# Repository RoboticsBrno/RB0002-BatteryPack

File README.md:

# RB0002-BatteryPack

Universal 2 cells Li-Ion battery pack with separate USB charger PCB for robot
power supplying.

This battery pack is designed for continuous 8.4 V / 15 A.

View this project on [CADLAB.io](https://cadlab.io/project/22740/).

License: [CC BY-SA 4.0](https://creativecommons.org/licenses/by-sa/4.0/?)

## Repository Structure

- `batteryPack` contains the main schematics and board drawing
- `doc` contains CubeMX pinout of the MCU, resistor calculation spreadsheet,
  etc.
- `footprints` contains the board-specific footprints
- `symbols` contains the board-specific symbols
- `tools` contains few scripts for automatization

## Building

Simply call `make` in the top-top level directory. The `build` directory will
them contain:

- split boards for the charger and the battery pack
- zipped gerbers for the boards you can directly use for manufacturing

Makefile uses [KiKit](https://github.com/yaqwsx/KiKit), therefore, it has to be
available on your system.

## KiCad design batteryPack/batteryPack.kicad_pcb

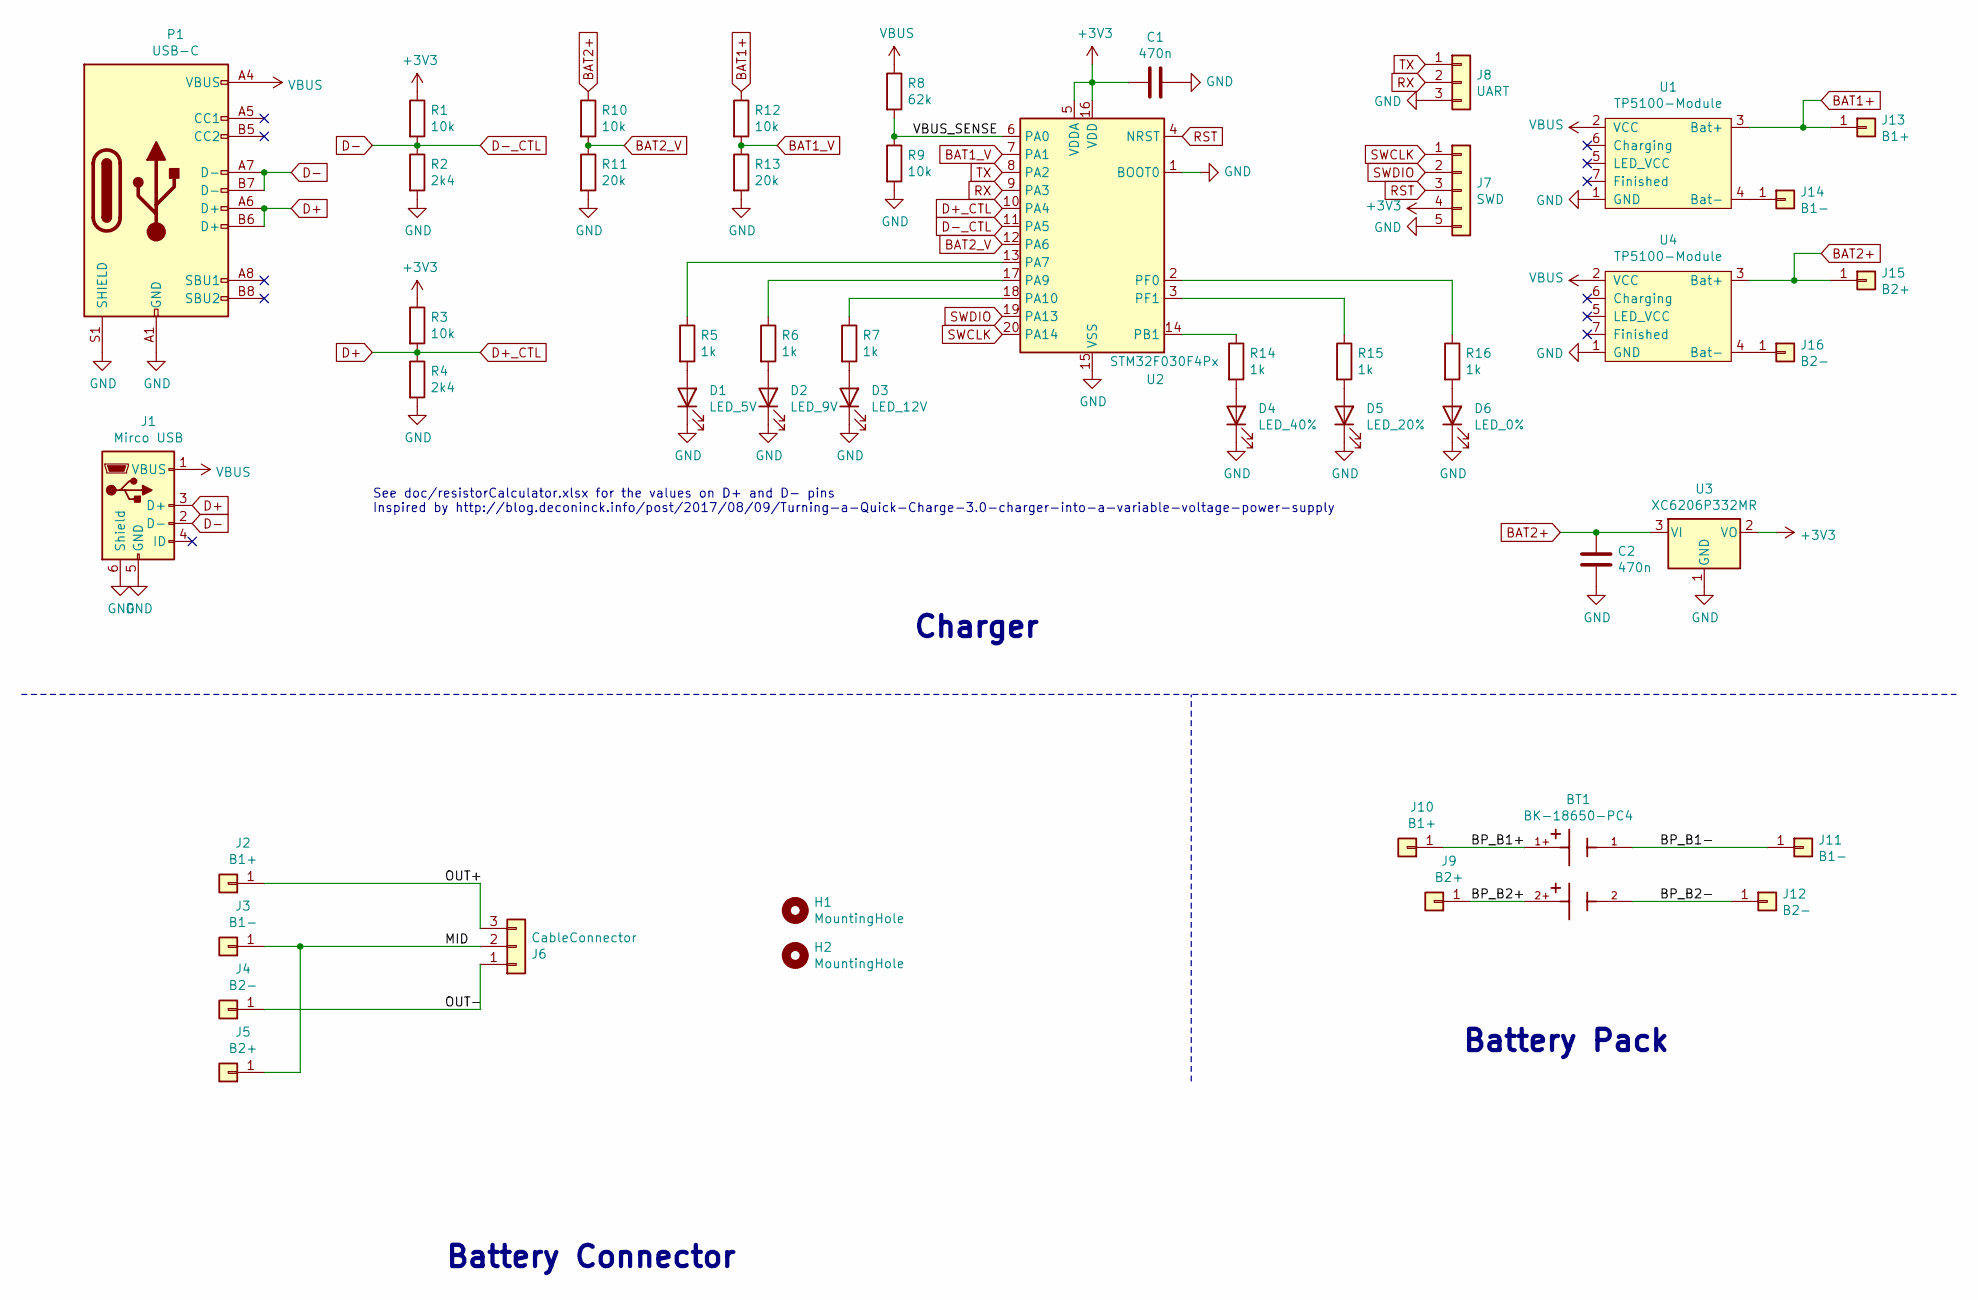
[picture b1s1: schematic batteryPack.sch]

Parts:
BT1: BK-18650-PC4; BAT_BK-18650-PC4
C1, C2: 470n; C_0603_1608Metric_Pad1.05x0.95mm_HandSolder
D1: LED_5V; LED_0603_1608Metric_Pad1.05x0.95mm_HandSolder
D2: LED_9V; LED_0603_1608Metric_Pad1.05x0.95mm_HandSolder
D3: LED_12V; LED_0603_1608Metric_Pad1.05x0.95mm_HandSolder
D4: LED_40%; LED_0603_1608Metric_Pad1.05x0.95mm_HandSolder
D5: LED_20%; LED_0603_1608Metric_Pad1.05x0.95mm_HandSolder
D6: LED_0%; LED_0603_1608Metric_Pad1.05x0.95mm_HandSolder
H1, H2: MountingHole; MountingHole_3.2mm_M3
J1: Mirco USB; USB_Micro-B_Wuerth_629105150521_CircularHoles
J2: B1+; 2mm_Banana-Vertical
J3: B1-; 2mm_Banana-Vertical
J4: B2-; 2mm_Banana-Vertical
J5: B2+; 2mm_Banana-Vertical
J6: CableConnector; Terminal_1x03_P5.08mm_Horizontal
J7: SWD; PinHeader_1x05_P2.54mm_Vertical
J8: UART; PinHeader_1x03_P2.54mm_Vertical
J9: B2+; 2mm_Banana-Socket
J10: B1+; 2mm_Banana-Socket
J11: B1-; 2mm_Banana-Socket
J12: B2-; 2mm_Banana-Socket
J13: B1+; 2mm_Banana-Plug
J14: B1-; 2mm_Banana-Plug
J15: B2+; 2mm_Banana-Plug
J16: B2-; 2mm_Banana-Plug
P1: USB-C; USB_C_Female-16Pin-HPJF
R1, R3, R9, R10, R12: 10k; R_0603_1608Metric_Pad1.05x0.95mm_HandSolder
R2, R4: 2k4; R_0603_1608Metric_Pad1.05x0.95mm_HandSolder
R5, R6, R7, R14, R15, R16: 1k; R_0603_1608Metric_Pad1.05x0.95mm_HandSolder
R8: 62k; R_0603_1608Metric_Pad1.05x0.95mm_HandSolder
R11, R13: 20k; R_0603_1608Metric_Pad1.05x0.95mm_HandSolder
U1, U4: TP5100-Module
U2: STM32F030F4Px; TSSOP-20_4.4x6.5mm_P0.65mm
U3: XC6206P332MR; SOT-23

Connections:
+3V3: C1.2, J7.4, R1.1, R3.1, U2.5 (VDDA), U2.16 (VDD), U3.2 (VO)
/BP_B1+: BT1.1+, J10.1
/BP_B1-: BT1.1 (1-), J11.1
/BP_B2+: BT1.2+, J9.1
/BP_B2-: BT1.2 (2-), J12.1
/MID: J3.1, J5.1, J6.2
/OUT+: J2.1, J6.3
/OUT-: J4.1, J6.1
/VBUS_SENSE: R8.2, R9.1, U2.6 (PA0)
BAT1+: J13.1, R12.1, U1.3 (Bat+)
BAT1_V: R12.2, R13.1, U2.7 (PA1)
BAT2+: C2.2, J15.1, R10.1, U3.3 (VI), U4.3 (Bat+)
BAT2_V: R10.2, R11.1, U2.12 (PA6)
D+: J1.3 (D+), P1.A6 (D+), P1.B6 (D+), R3.2, R4.1, U2.10 (PA4)
D-: J1.2 (D-), P1.A7 (D-), P1.B7 (D-), R1.2, R2.1, U2.11 (PA5)
GND: C1.1, C2.1, D1.1 (K), D2.1 (K), D3.1 (K), D4.1 (K), D5.1 (K), D6.1 (K), J1.5 (GND), J1.6 (Shield), J7.5, J8.3, P1.A1 (GND), P1.A12 (GND), P1.B1 (GND), P1.B12 (GND), P1.S1 (SHIELD), R2.2, R4.2, R9.2, R11.2, R13.2, U1.1 (GND), U2.1 (BOOT0), U2.15 (VSS), U3.1 (GND), U4.1 (GND)
unnamed: D1.2 (A), R5.2
unnamed: D2.2 (A), R6.2
unnamed: D3.2 (A), R7.2
unnamed: D4.2 (A), R14.2
unnamed: D5.2 (A), R15.2
unnamed: D6.2 (A), R16.2
unnamed: J14.1, U1.4 (Bat-)
unnamed: J16.1, U4.4 (Bat-)
unnamed: R5.1, U2.13 (PA7)
unnamed: R6.1, U2.17 (PA9)
unnamed: R7.1, U2.18 (PA10)
unnamed: R14.1, U2.14 (PB1)
unnamed: R15.1, U2.3 (PF1)
unnamed: R16.1, U2.2 (PF0)
RST: J7.3, U2.4 (NRST)
RX: J8.2, U2.9 (PA3)
SWCLK: J7.1, U2.20 (PA14)
SWDIO: J7.2, U2.19 (PA13)
TX: J8.1, U2.8 (PA2)
VBUS: J1.1 (VBUS), P1.A4 (VBUS), P1.A9 (VBUS), P1.B4 (VBUS), P1.B9 (VBUS), R8.1, U1.2 (VCC), U4.2 (VCC)

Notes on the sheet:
Battery Pack
Charger
Battery Connector
See doc/resistorCalculator.xlsx for the values on D+ and D- pins Inspired by http://blog.deconinck.info/post/2017/08/09/Turning-a-Quick-Charge-3.0-charger-into-a-variable-voltage-power-supply

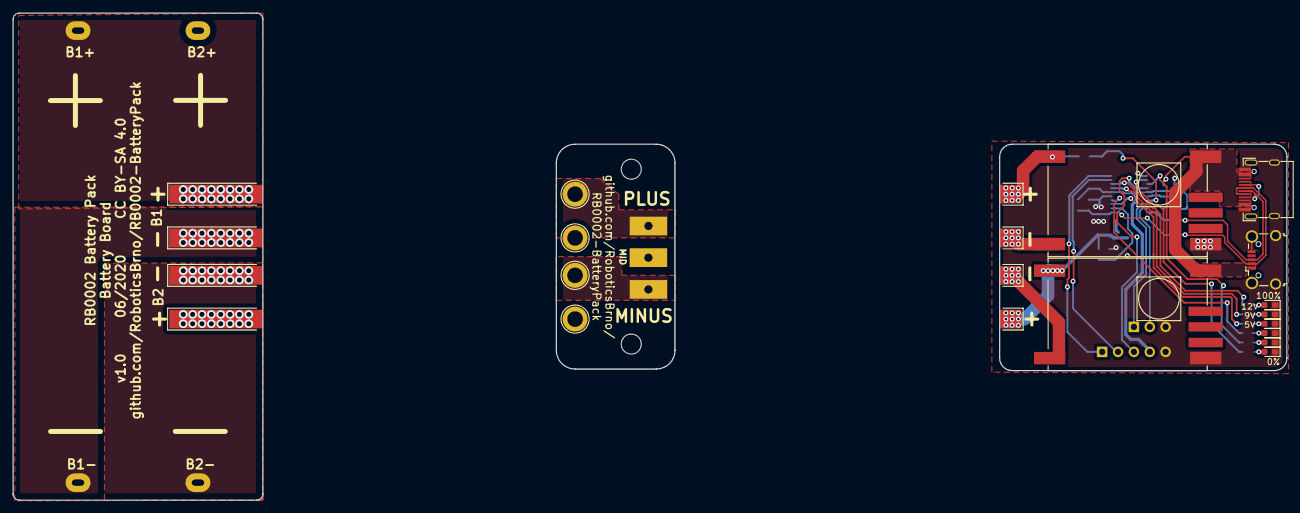
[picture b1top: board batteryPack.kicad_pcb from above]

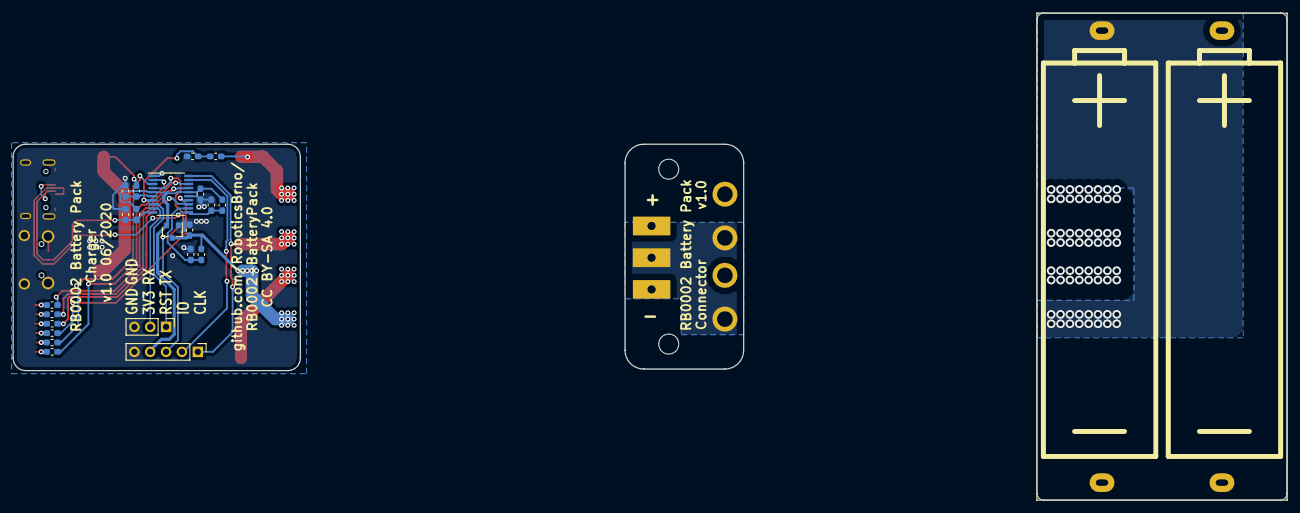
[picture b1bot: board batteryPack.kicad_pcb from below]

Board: 2 copper layers, 204.0 x 78.0 mm, 48 parts (23 on the bottom side), 36 nets.

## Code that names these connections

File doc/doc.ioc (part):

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Mcu.Name=STM32F030F4Px
Mcu.Package=TSSOP20
Mcu.UserName=STM32F030F4Px
PA0.Mode=IN0
PA0.Signal=ADC_IN0
PA1.Mode=IN1
PA1.Signal=ADC_IN1
PA10.Signal=GPIO_Output
PA13.Mode=Serial_Wire
PA13.Signal=SYS_SWDIO
PA14.Mode=Serial_Wire
PA14.Signal=SYS_SWCLK
PA2.Mode=Asynchronous
PA2.Signal=USART1_TX
PA3.Mode=Asynchronous
PA3.Signal=USART1_RX
PA6.Mode=IN6
PA6.Signal=ADC_IN6
PA7.Signal=GPIO_Output
PA9.Signal=GPIO_Output
PB1.Signal=GPIO_Output
PF0-OSC_IN.Signal=GPIO_Output
PF1-OSC_OUT.Signal=GPIO_Output
board=custom

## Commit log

2020-03-31 Prepare initial structure
2020-03-31 README.md: Add info about battery pack and USB charger
2020-04-01 Add documentation
2020-04-01 Finish first draft of the schematics
2020-04-01 Add fooprints
2020-04-01 Sketch out initial component layout
2020-04-01 Route battery and the connector
2020-04-01 Route the charger
2020-04-01 Make the labels nice
2020-04-01 Update Makefile for all three subboards
2020-04-02 Add battery holder 3D model
2020-04-02 Fine tune the board based on the feedback
2020-04-07 Migrate Makefile to KiKit
2020-04-08 Generate page using KiKit
2020-04-08 Add radius to panels
2020-04-21 Fine tune TP5100 footprint
2020-04-21 Migrate to KiKit 0.3
2020-04-26 Fix erroreous charger extraction
2020-04-29 Swap layers on battery board
2020-04-29 Add tenons and handle to the battery
2020-04-29 Change connector to screw terminal
2020-05-05 Tune pull handle and battery panel
2020-05-06 Add battery voltage signalization
2020-05-08 Add silkscreen text + LICENSE
    - add version info text to Charger board
    - add +/- text for Charger and Connector board
    - add license Creative Commons BY-SA 4.0
2020-06-17 Remove tenons from the battery
2020-06-17 Make ptich of battery holder smaller
2020-06-17 Mark the battery polarity on the other side
2020-06-17 Make room for mouse bites
2020-06-17 Bump version on silkscreen to 1.0
2020-06-17 Modify Makefile panelization for manufactoring
    - replace mousebits with V-cuts on battery board (after removing tenons it is posible to use V-cuts)
    - replace V-cut with mousebites on charge board due to PCBA
2020-07-08 Add initial FW (signaling, no QC)
2020-07-08 Add initial firmware version
2020-07-08 Implement QuickCharge
2020-07-09 Add filtering of bus voltage
2020-07-09 Add testing FW
2020-12-09 uvolneni enkoderu
    - dolomitelny enkoder
    - zmenseni via u civek LDC
    - vymena pouzdra USB-C
    - otoceni IR prijmace
    - zakas vilivani medi pod BMX9555
    - odstraneni "ochrannych" odporu k M41T62
2020-12-09 Deploy RoboticsBrno/RB0002-BatteryPack to github.com/RoboticsBrno/RB0002-BatteryPack.git:gh-pages

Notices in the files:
batteryPack/batteryPack.kicad_pcb:
v1.0 06/2020 CC BY-SA 4.0
